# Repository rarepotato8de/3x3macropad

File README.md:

# 3x3macropad: Affordable & Cool!

[Showcase](#showcase) | [Highlight Features](#highlights) | [How this Project started](#how-this-project-started) | [Build Guide](BUILD_GUIDE.md) | [QMK/VIAL Guide](QMK_GUIDE.md) | [Thanks to..](#credits)

----

Can be fully customized and programmed to your needs. It's running QMK or VIAL and has some super cool features!

## Highlights

* 6 (up to 9) Mechanical Switches
* EC11 Encoder (Knob)
* **Hotswap** Sockets
* **OLED Screen**
* RGB **Underglow**
* USB-C Connector (if you choose a USB-C ProMicro!)
* Runs with QMK (VIAL) - freely programmable
* Works with all major OSs, no driver needed

The coolest part of the macropad is the OLED Display on which you can display images, text and small animations<br/>
> [!NOTE]  
> This is an older version, where the screws are on the switch plate. It's only for showcasing the OLED animation

## Required parts

* 6x to 9x Hotswap Sockets
* 1x Arduino Pro Micro
* 1x Bottom plate, 1x PCB, 1x Switch plate
* 4x 10mm M2 Standoffs
* 8x ~5mm M2 Screws
* Mechanical MX Switches
* Keycaps
* optional: 6x SMD WS2812B LED's
* optional: 1x EC11 Encoder (15mm)
* optional: 1x 0.91" OLED Display

## Showcase

More images of slightly older versions can be found [here](MORE_IMAGES.md)!

## How this Project started

It all started in August 2021 when I had the first contact with custom mechanical keyboards which I've seen on youtube. I was immediately interested since I've been using membrane since I had a PC - never had a mechanical keyboard. So I wanted to get myself a decent mechanical keyboard: The problem was, I wasn't sure on what to get.
So I read myself deeper into this Hobby and was especially interested in creating something myself - PCB's. And I did it!
Started off with reading ai03's PCB guide which is really good and then thought about what would be affordable to make but also nice to use.

Small keyboards (macropads) came in my mind: I've seen some in the past, but they were quite expensive and just not as cool as I would like them to be.
So I wrote down what features I would like to have: OLED, small form factor, Encoder. After that, it was time to design it.

The Layout of this Macropads actually was the first thing I had in mind and it turned out way better than expected when I got my first PCB's.
Besides that, the case-less design was inspired by the custom keyboard I wanted to have at that time: Discipline65 - which I'm using now.
Not only does it look industrial and cool, but it also saves costs for a "dedicated" case.

Shortly after I build my first macropad and shared pictures of it, I noticed that there is quite a high demand for it. So I started offering them.

Now we here. 

In the past weeks I've gotten much love and appreciation from so many people who like my project. Thanks for that! 💜💜💜

**2024 Update:** After quite some time I got more into Git(Hub) and since I always loved and used open-source projects myself, I open-sourced this project!
You can now order the PCB's and all other stuff yourself. The PCB files (Gebers) can be uploaded to any PCB Manufacturer (e.g. JLCPCB) and be ordered for very cheap.

## Credits

Thanks to @mondrian for not only getting yourself 5 macropads, but also for creating the awesome pictures for the [Build Guide](BUILD_GUIDE.md)! 😎

## Questions?

Please feel free to message me

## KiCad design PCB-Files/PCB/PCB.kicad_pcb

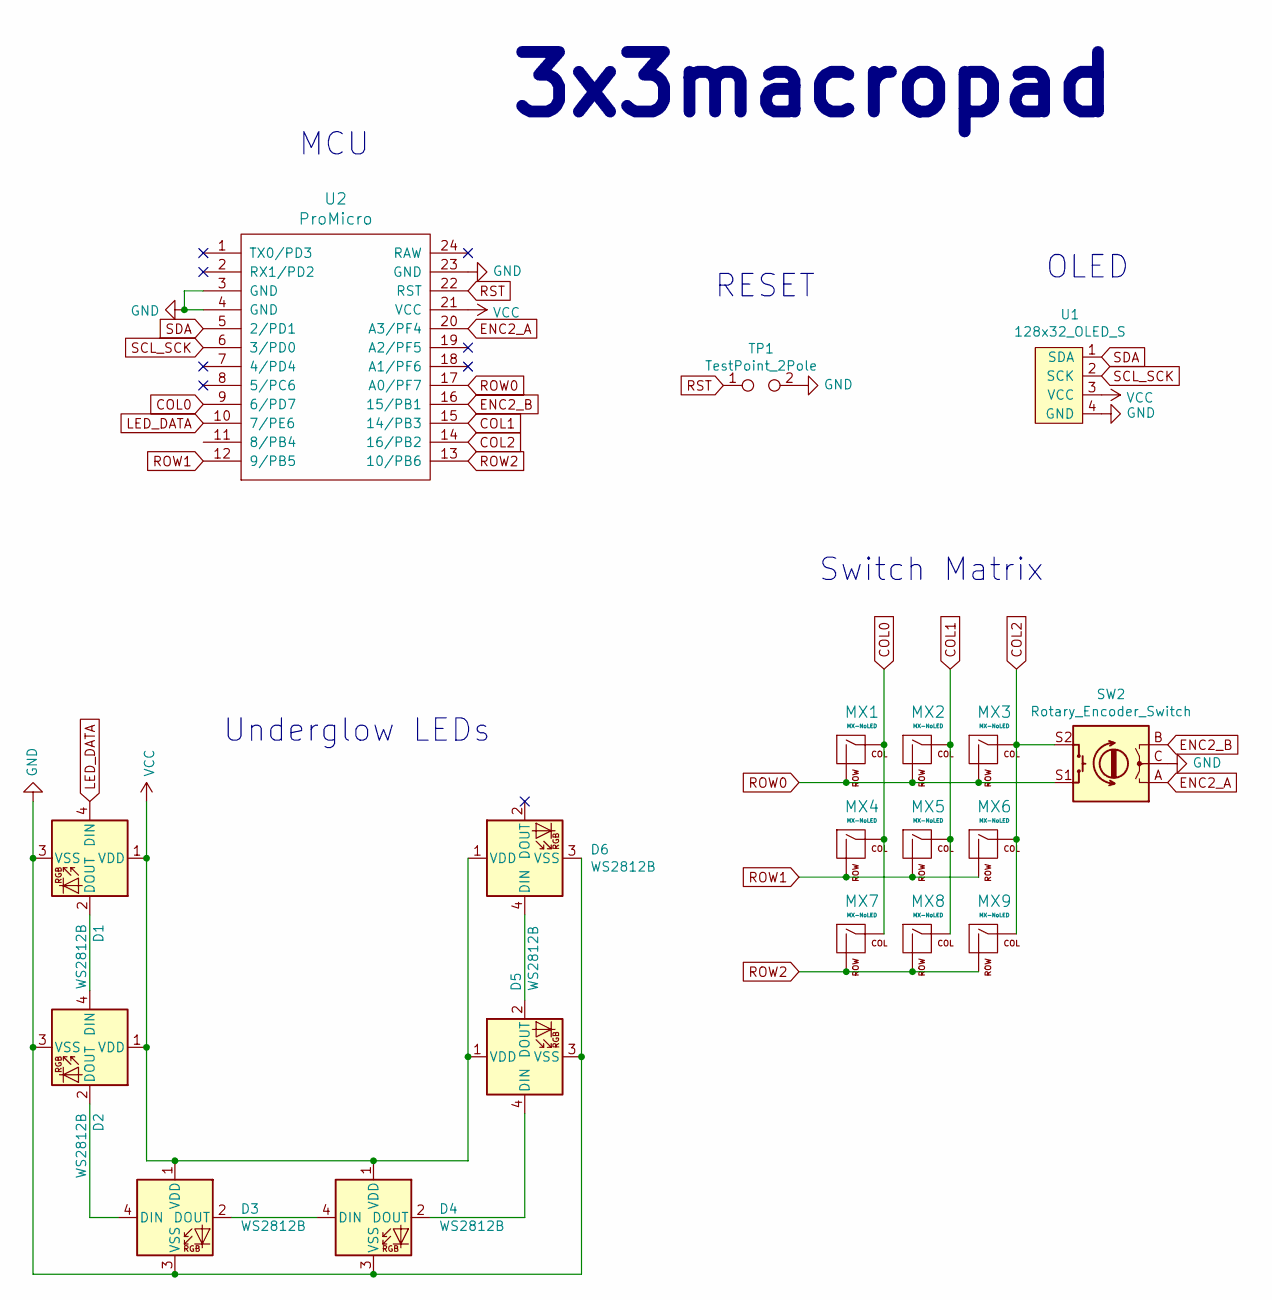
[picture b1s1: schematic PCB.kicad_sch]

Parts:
D1, D2, D3, D4, D5, D6: WS2812B; LED_WS2812B_PLCC4_5.0x5.0mm_P3.2mm
MX1, MX2, MX3, MX4, MX5, MX6, MX7, MX8, MX9: MX-NoLED; MXOnly-1U-Hotswap
SW2: Rotary_Encoder_Switch; RotaryEncoder_Alps_EC11E-Switch_Vertical_H20mm
TP1: TestPoint_2Pole; TestPoint_2Pads_Pitch2.54mm_Drill0.8mm
U1: 128x32_OLED_S; 128x32_OLED_F_ROTATE
U2: ProMicro; ArduinoProMicro-ZigZag

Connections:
COL0: MX1.1 (COL), MX4.1 (COL), MX7.1 (COL), U2.9 (6/PD7)
COL1: MX2.1 (COL), MX5.1 (COL), MX8.1 (COL), U2.15 (14/PB3)
COL2: MX3.1 (COL), MX6.1 (COL), MX9.1 (COL), SW2.S2, U2.14 (16/PB2)
ENC2_A: SW2.A, U2.20 (A3/PF4)
ENC2_B: SW2.B, U2.16 (15/PB1)
GND: D1.3 (VSS), D2.3 (VSS), D3.3 (VSS), D4.3 (VSS), D5.3 (VSS), D6.3 (VSS), SW2.C, TP1.2, U1.4 (GND), U2.3 (GND), U2.4 (GND), U2.23 (GND)
LED_DATA: D1.4 (DIN), U2.10 (7/PE6)
unnamed: D1.2 (DOUT), D2.4 (DIN)
unnamed: D2.2 (DOUT), D3.4 (DIN)
unnamed: D3.2 (DOUT), D4.4 (DIN)
unnamed: D4.2 (DOUT), D5.4 (DIN)
unnamed: D5.2 (DOUT), D6.4 (DIN)
ROW0: MX1.2 (ROW), MX2.2 (ROW), MX3.2 (ROW), SW2.S1, U2.17 (A0/PF7)
ROW1: MX4.2 (ROW), MX5.2 (ROW), MX6.2 (ROW), U2.12 (9/PB5)
ROW2: MX7.2 (ROW), MX8.2 (ROW), MX9.2 (ROW), U2.13 (10/PB6)
RST: TP1.1, U2.22 (RST)
SCL_SCK: U1.2 (SCK), U2.6 (3/PD0)
SDA: U1.1 (SDA), U2.5 (2/PD1)
VCC: D1.1 (VDD), D2.1 (VDD), D3.1 (VDD), D4.1 (VDD), D5.1 (VDD), D6.1 (VDD), U1.3 (VCC), U2.21 (VCC)

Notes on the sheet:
RESET
Switch Matrix
3x3macropad
Underglow LEDs
OLED
MCU

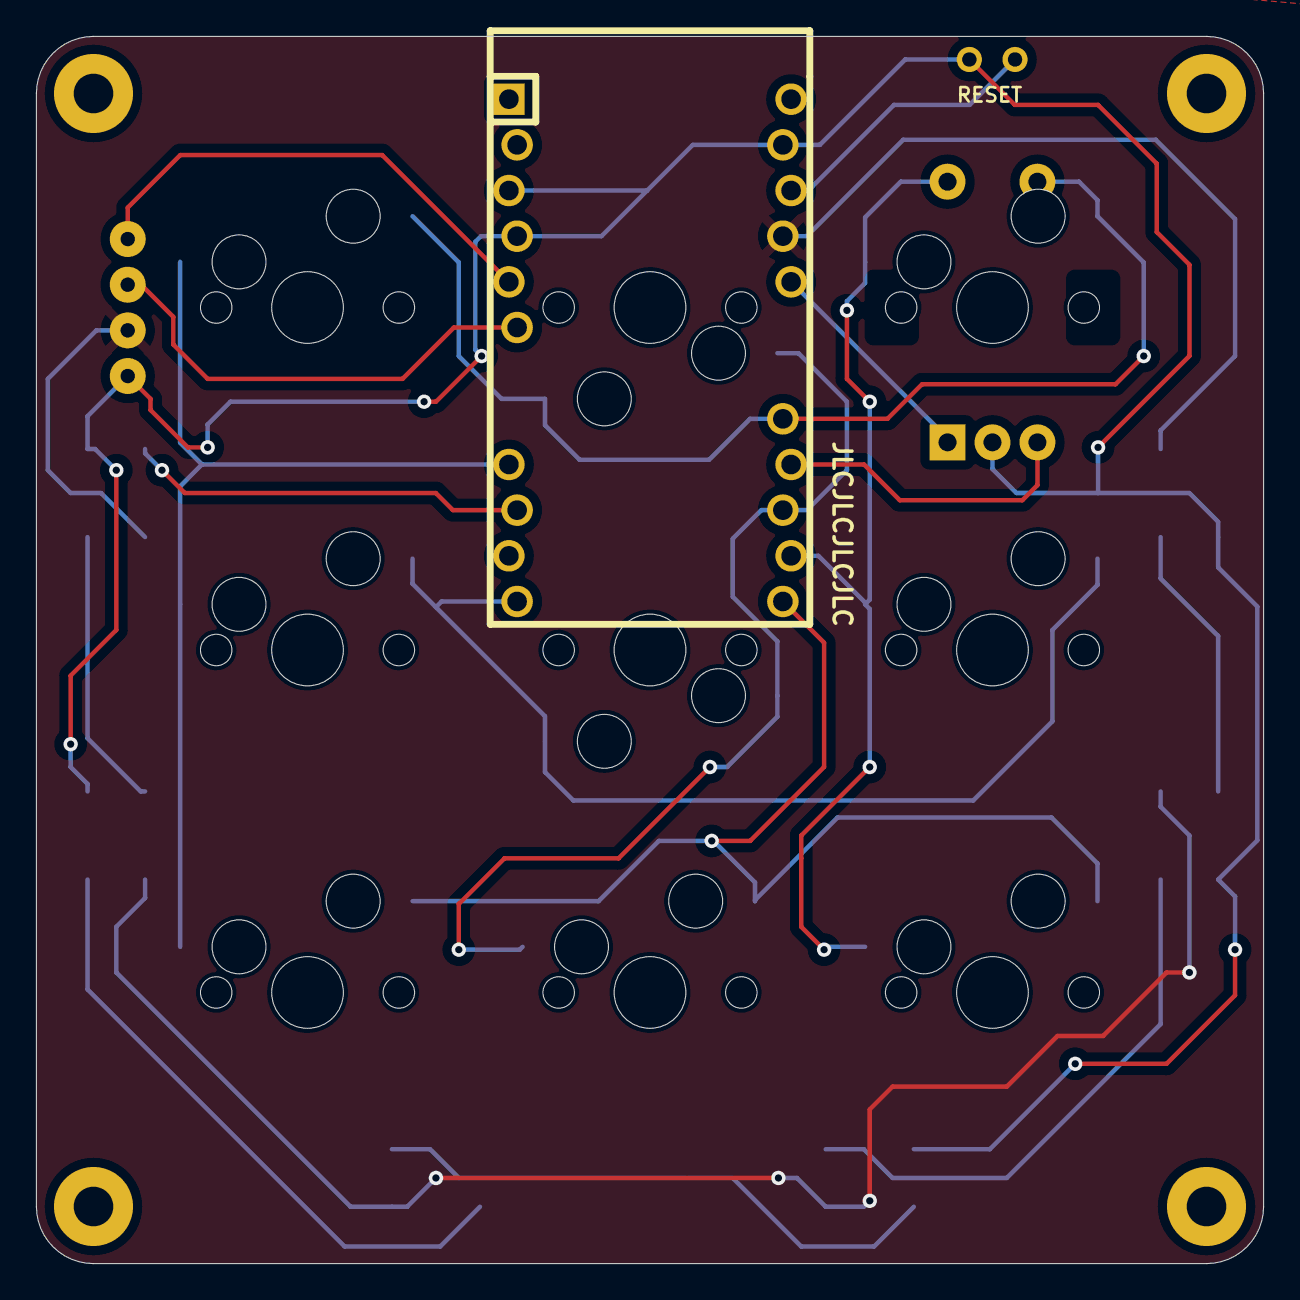
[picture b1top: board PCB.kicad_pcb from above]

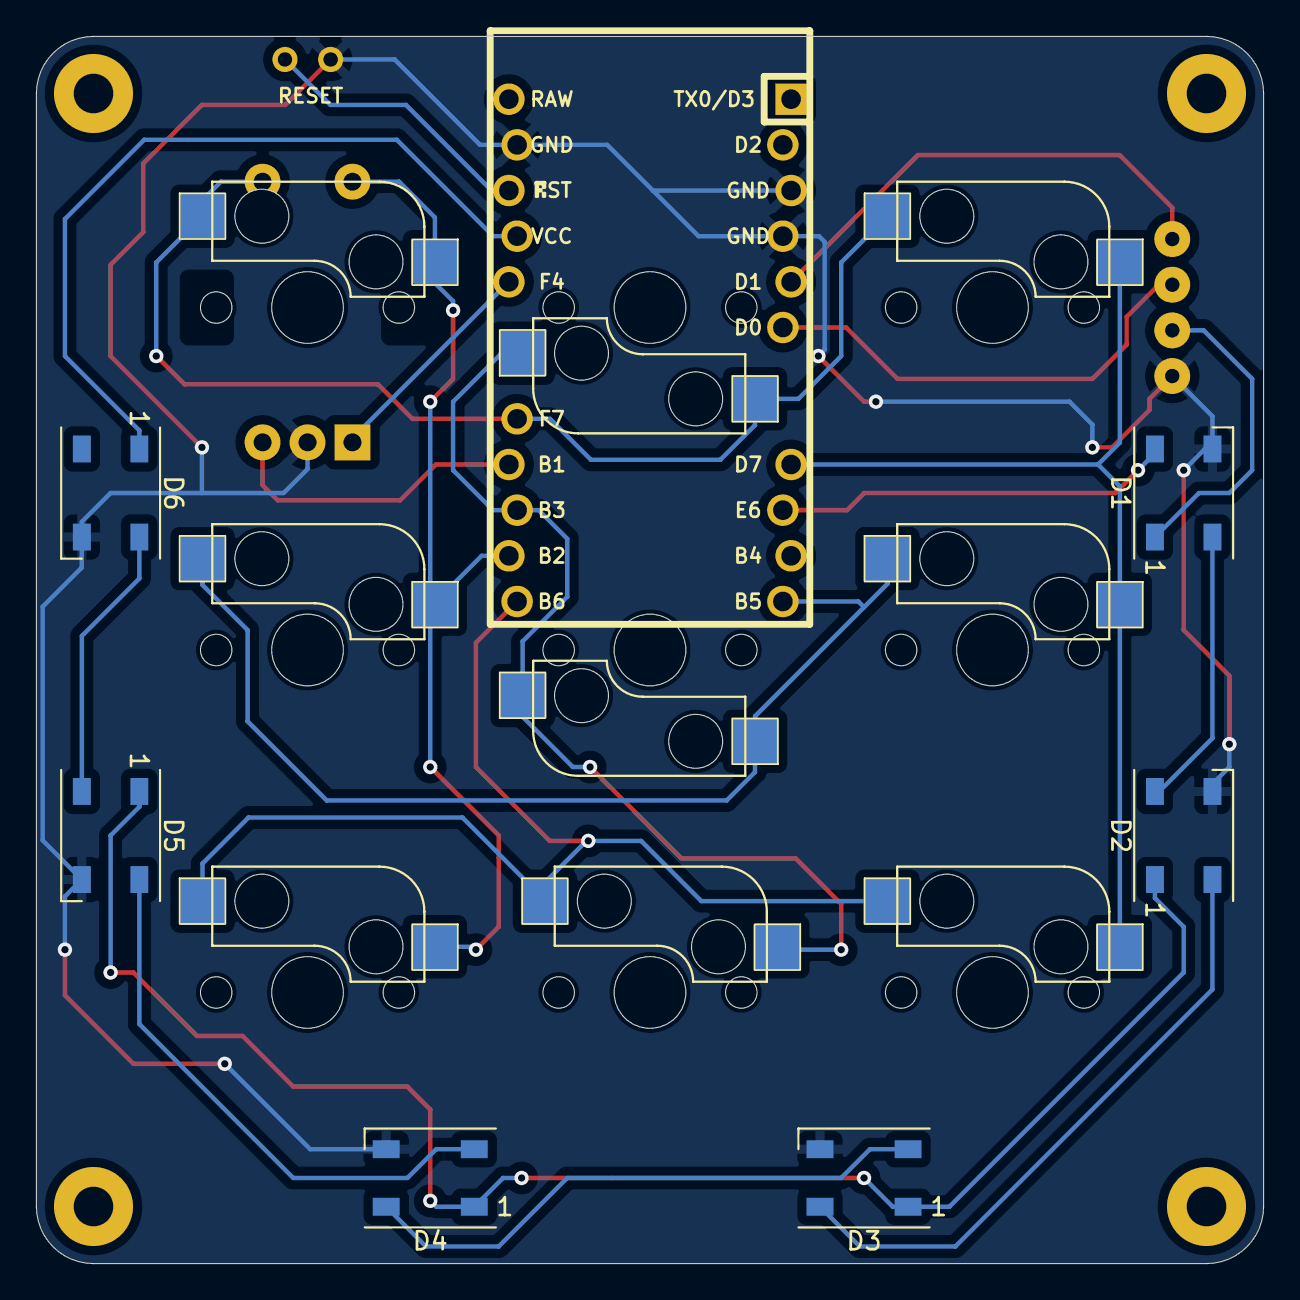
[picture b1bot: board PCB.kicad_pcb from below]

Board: 2 copper layers, 68.3 x 68.3 mm, 19 parts (6 on the bottom side), 19 nets.

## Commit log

2024-04-23 PCB Files published
    PCB Files for KiCad 7.0
    Minor changes to my previous version, technically untested but surely works
    - No changes to schematic
    - Footprints/Symbols Updated
    - Gerber Files
2024-05-28 Create BUILD_GUIDE.md
    Adding build guide
2024-05-28 build guide pics
2024-07-26 Update README.md
    new picture
